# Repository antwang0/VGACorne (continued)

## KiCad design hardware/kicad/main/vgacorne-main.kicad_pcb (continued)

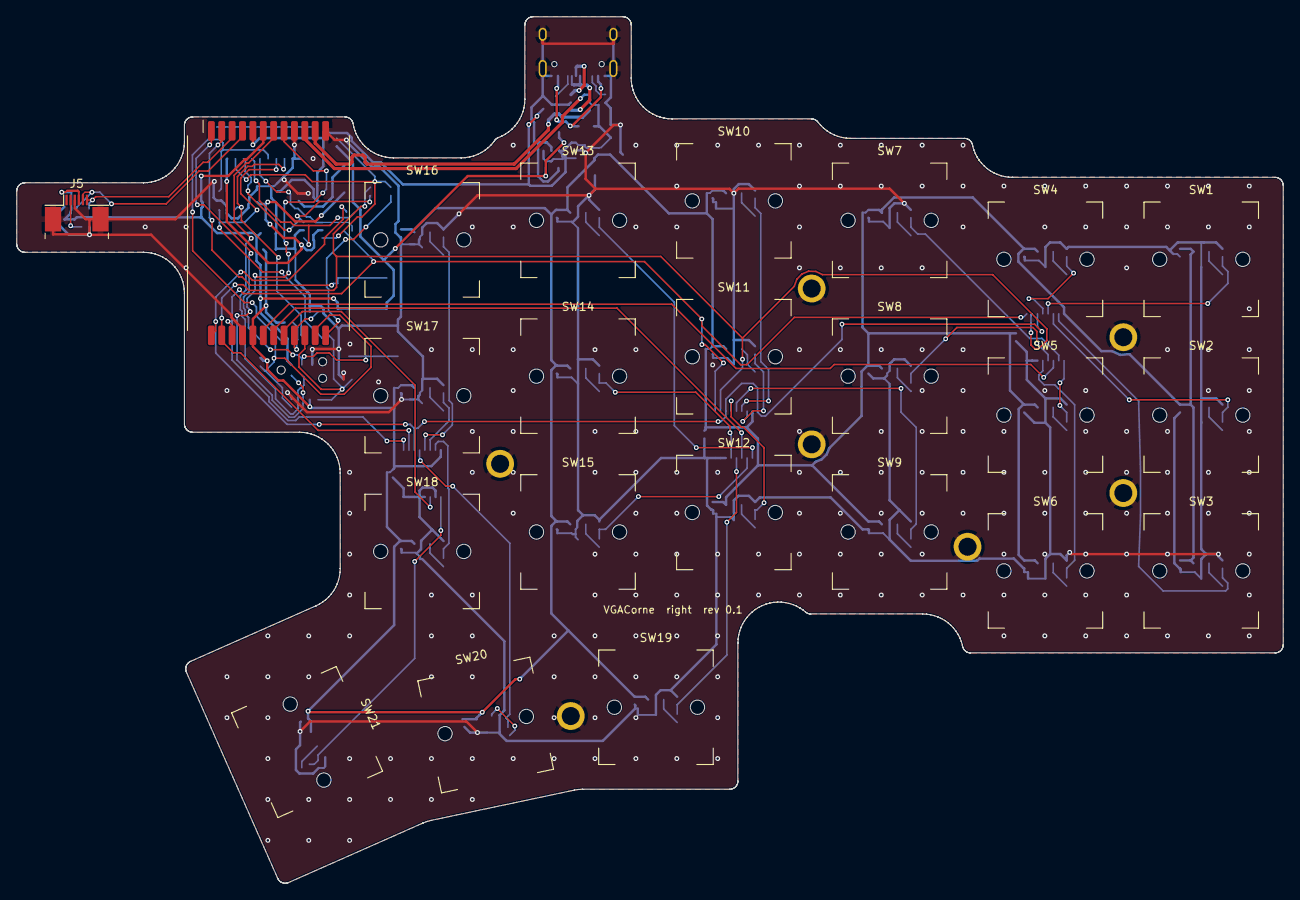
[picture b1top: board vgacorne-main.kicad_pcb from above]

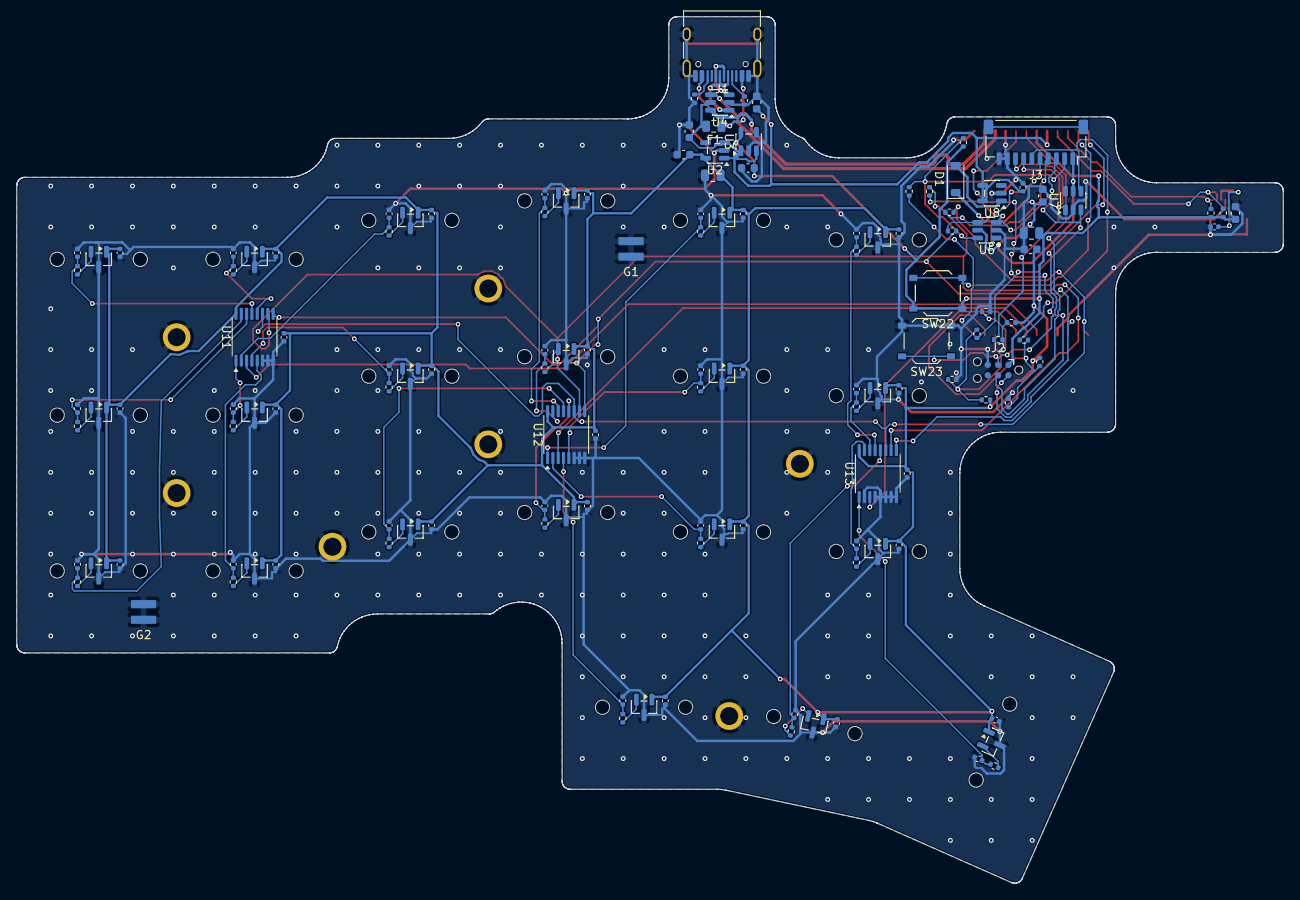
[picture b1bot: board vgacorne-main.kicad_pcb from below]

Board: 2 copper layers, 154.9 x 105.9 mm, 164 parts (134 on the bottom side), 79 nets.

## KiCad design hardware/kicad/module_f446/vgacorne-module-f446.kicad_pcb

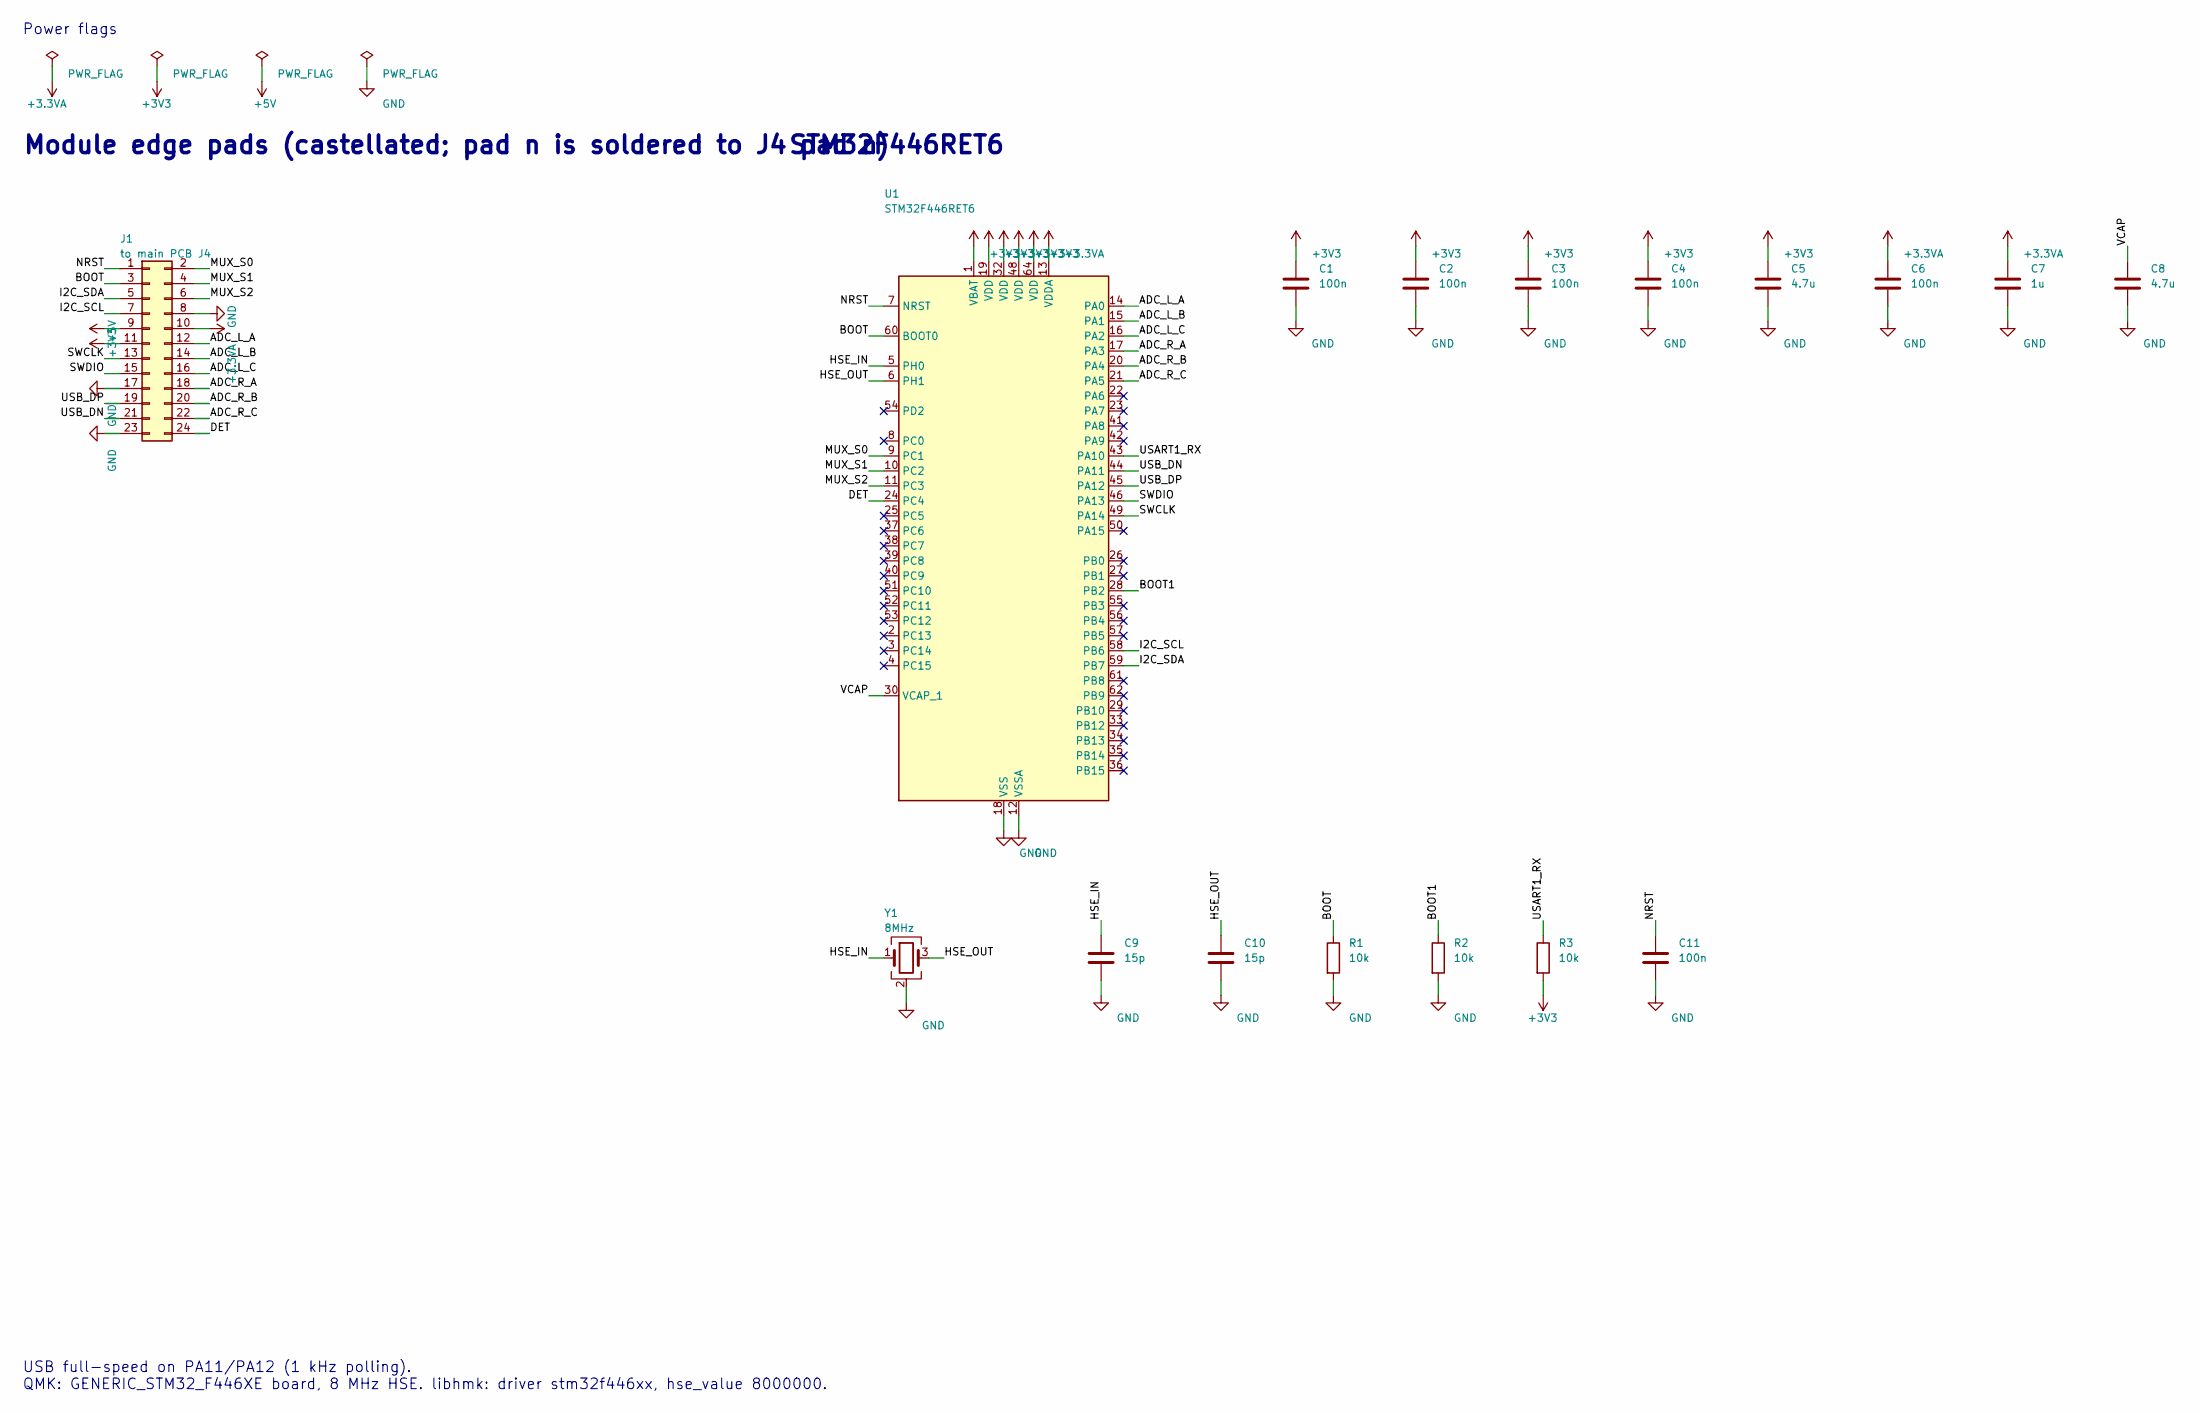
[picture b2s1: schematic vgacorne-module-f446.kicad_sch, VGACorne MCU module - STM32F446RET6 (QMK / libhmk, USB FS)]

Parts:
C1, C2, C3, C4, C6, C11: 100n; C_0402_1005Metric
C5, C8: 4.7u; C_0603_1608Metric
C7: 1u; C_0603_1608Metric
C9, C10: 15p; C_0402_1005Metric
J1: to main PCB J4; Module_Castellated_2x12_P1.27mm_19.4x25mm
R1, R2, R3: 10k; R_0402_1005Metric
U1: STM32F446RET6; LQFP-64_10x10mm_P0.5mm; MPN STM32F446RET6
Y1: 8MHz; Crystal_SMD_3225-4Pin_3.2x2.5mm; MPN X32258MOB4SI

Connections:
+3.3VA: C6.1, C7.1, J1.10, U1.13 (VDDA)
+3V3: C1.1, C2.1, C3.1, C4.1, C5.1, J1.11, R3.2, U1.1 (VBAT), U1.19 (VDD), U1.32 (VDD), U1.48 (VDD), U1.64 (VDD)
+5V: J1.9
/ADC_L_A: J1.12, U1.14 (PA0)
/ADC_L_B: J1.14, U1.15 (PA1)
/ADC_L_C: J1.16, U1.16 (PA2)
/ADC_R_A: J1.18, U1.17 (PA3)
/ADC_R_B: J1.20, U1.20 (PA4)
/ADC_R_C: J1.22, U1.21 (PA5)
/BOOT: J1.3, R1.1, U1.60 (BOOT0)
/BOOT1: R2.1, U1.28 (PB2)
/DET: J1.24, U1.24 (PC4)
/HSE_IN: C9.1, U1.5 (PH0), Y1.1
/HSE_OUT: C10.1, U1.6 (PH1), Y1.3
/I2C_SCL: J1.7, U1.58 (PB6)
/I2C_SDA: J1.5, U1.59 (PB7)
/MUX_S0: J1.2, U1.9 (PC1)
/MUX_S1: J1.4, U1.10 (PC2)
/MUX_S2: J1.6, U1.11 (PC3)
/NRST: C11.1, J1.1, U1.7 (NRST)
/SWCLK: J1.13, U1.49 (PA14)
/SWDIO: J1.15, U1.46 (PA13)
/USART1_RX: R3.1, U1.43 (PA10)
/USB_DN: J1.21, U1.44 (PA11)
/USB_DP: J1.19, U1.45 (PA12)
/VCAP: C8.1, U1.30 (VCAP_1)
GND: C1.2, C2.2, C3.2, C4.2, C5.2, C6.2, C7.2, C8.2, C9.2, C10.2, C11.2, J1.8, J1.17, J1.23, R1.2, R2.2, U1.12 (VSSA), U1.18 (VSS), U1.31 (VSS), U1.47 (VSS), U1.63 (VSS), Y1.2 (G), Y1.4 (G)

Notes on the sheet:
Module edge pads (castellated; pad n is soldered to J4 pad n)
STM32F446RET6
USB full-speed on PA11/PA12 (1 kHz polling). QMK: GENERIC_STM32_F446XE board, 8 MHz HSE. libhmk: driver stm32f446xx, hse_value 8000000.
Power flags

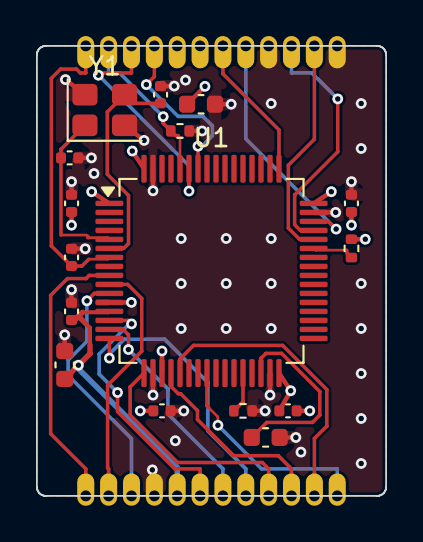
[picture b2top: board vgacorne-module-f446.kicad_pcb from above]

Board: 4 copper layers, 19.4 x 25.0 mm, 17 parts (0 on the bottom side), 26 nets.

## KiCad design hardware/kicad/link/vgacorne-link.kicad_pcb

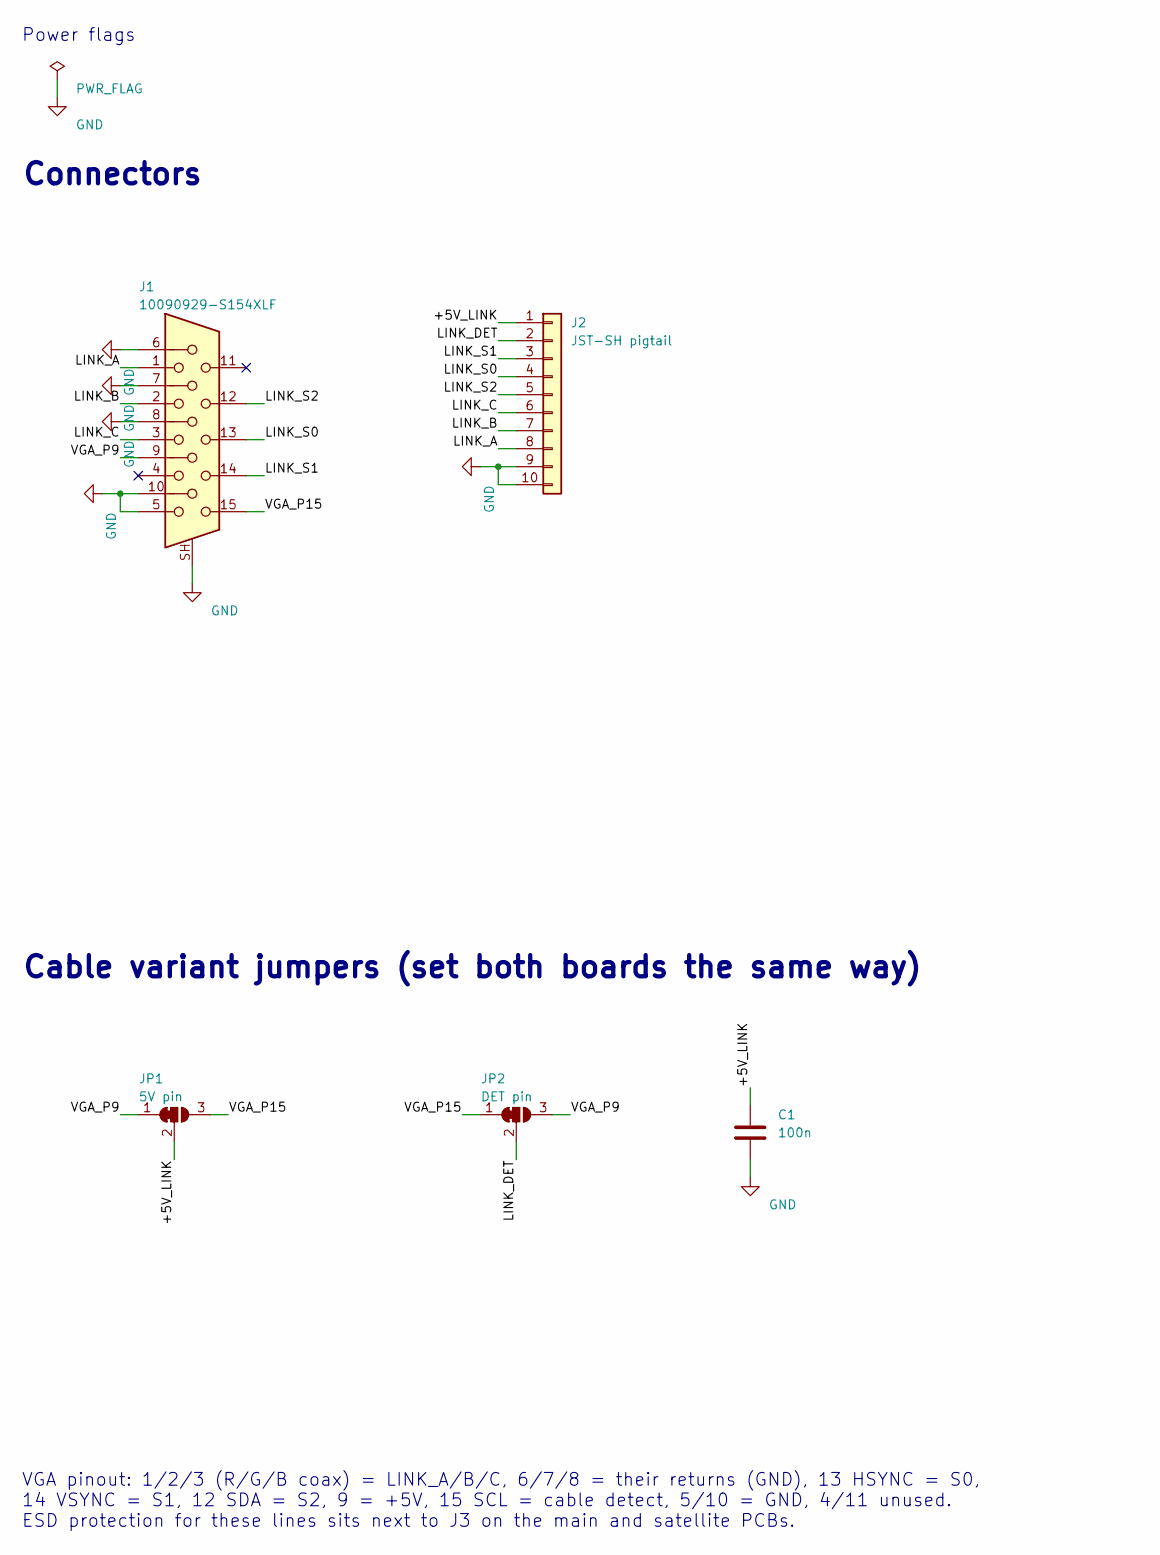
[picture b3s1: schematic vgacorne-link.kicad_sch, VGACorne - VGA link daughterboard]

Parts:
C1: 100n; C_0402_1005Metric
J1: 10090929-S154XLF; DSUB-15-HD_Socket_Vertical_P2.29x1.98mm_Amphenol_10090929; MPN Amphenol FCI 10090929-S154XLF
J2: JST-SH pigtail; WirePads_1x10_P1.6mm
JP1: 5V pin; SolderJumper-3_P1.3mm_Bridged12_RoundedPad1.0x1.5mm
JP2: DET pin; SolderJumper-3_P1.3mm_Bridged12_RoundedPad1.0x1.5mm

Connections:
/+5V_LINK: C1.1, J2.1, JP1.2 (C)
/LINK_A: J1.1, J2.8
/LINK_B: J1.2, J2.7
/LINK_C: J1.3, J2.6
/LINK_DET: J2.2, JP2.2 (C)
/LINK_S0: J1.13, J2.4
/LINK_S1: J1.14, J2.3
/LINK_S2: J1.12, J2.5
/VGA_P9: J1.9, JP1.1 (A), JP2.3 (B)
/VGA_P15: J1.15, JP1.3 (B), JP2.1 (A)
GND: C1.2, J1.5, J1.6, J1.7, J1.8, J1.10, J1.SH, J2.9, J2.10

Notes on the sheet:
Connectors
Cable variant jumpers (set both boards the same way)
VGA pinout: 1/2/3 (R/G/B coax) = LINK_A/B/C, 6/7/8 = their returns (GND), 13 HSYNC = S0, 14 VSYNC = S1, 12 SDA = S2, 9 = +5V, 15 SCL = cable detect, 5/10 = GND, 4/11 unused. ESD protection for these lines sits next to J3 on the main and satellite PCBs.
Power flags

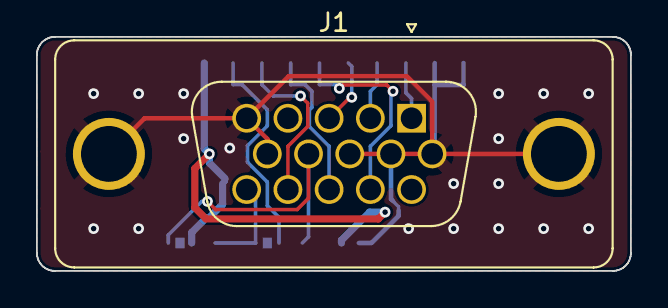
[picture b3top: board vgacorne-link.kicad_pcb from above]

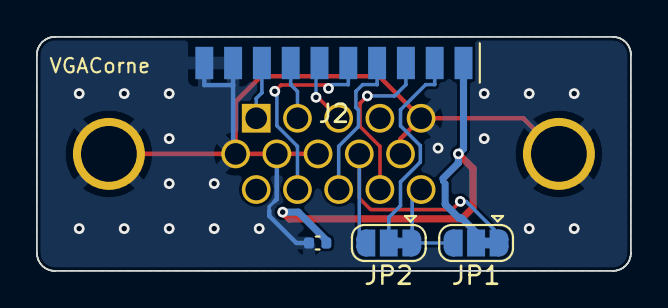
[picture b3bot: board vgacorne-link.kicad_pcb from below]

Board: 2 copper layers, 33.0 x 13.0 mm, 5 parts (4 on the bottom side), 11 nets.

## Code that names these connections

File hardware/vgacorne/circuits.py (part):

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# LQFP-64 pins used for keyboard signals. The AT32F405RCT7 and STM32F446RET6 share
# these pin numbers, so both modules (and their firmware configs) use the same map.
MCU_SIGNAL_PINS = {
    "14": "ADC_L_A", "15": "ADC_L_B", "16": "ADC_L_C",  # PA0..PA2: local muxes
    "17": "ADC_R_A", "20": "ADC_R_B", "21": "ADC_R_C",  # PA3..PA5: satellite muxes
    "9": "MUX_S0", "10": "MUX_S1", "11": "MUX_S2",  # PC1..PC3
    "24": "DET",  # PC4
    "7": "NRST", "60": "BOOT", "46": "SWDIO", "49": "SWCLK",  # NRST, BOOT0, PA13, PA14
    "58": "I2C_SCL", "59": "I2C_SDA",  # PB6/PB7: I2C1 (AF4 on the STM32, MUX4 on the AT32)
}
# firmware.py derives libhmk's select/input pin names from these by tracing the netlists.

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        R("R20", "4.7k", "I2C_SDA", "+3V3", "trackpad"),
        C("C16", "1u", "+3V3", "GND", "trackpad", fp=C0603),
    ]
    if "TP_NRST" in PAD.connector_pins.values():  # internal pull-up; Azoteq recommends 100 nF
        p.append(C("C17", "100n", "TP_NRST", "GND", "trackpad"))
    # Link to the satellite (via the VGA daughterboard)
    pull_up = SENSOR.invert_adc  # pull toward "released" when the cable is absent
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        Part("JP1", "Jumper:SolderJumper_3_Bridged12", "5V pin", "Jumper:SolderJumper-3_P1.3mm_Bridged12_RoundedPad1.0x1.5mm",
             {"1": "VGA_P9", "2": "+5V_LINK", "3": "VGA_P15"}, "jumpers",
             description="+5 V on VGA pin 9 (default) or pin 15 (for 3+4 cables without pin 9)"),
        Part("JP2", "Jumper:SolderJumper_3_Bridged12", "DET pin", "Jumper:SolderJumper-3_P1.3mm_Bridged12_RoundedPad1.0x1.5mm",
             {"1": "VGA_P15", "2": "LINK_DET", "3": "VGA_P9"}, "jumpers",
             description="Cable-detect on VGA pin 15 (default) or pin 9; always set opposite to JP1"),
        C("C1", "100n", "+5V_LINK", "GND", "jumpers"),
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        ("jumpers", "Cable variant jumpers (set both boards the same way)", (20.32, 150.0), 250),
    ]
    notes = [
        ("VGA pinout: 1/2/3 (R/G/B coax) = LINK_A/B/C, 6/7/8 = their returns (GND), 13 HSYNC = S0,\n"
         "14 VSYNC = S1, 12 SDA = S2, 9 = +5V, 15 SCL = cable detect, 5/10 = GND, 4/11 unused.\n"
         "ESD protection for these lines sits next to J3 on the main and satellite PCBs.", (20.32, 230.0)),
    ]
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        C("C9", XTAL_CAP, "HSE_IN", "GND", "mcu"), C("C10", XTAL_CAP, "HSE_OUT", "GND", "mcu"),
        R("R1", "10k", "BOOT", "GND", "mcu", description="BOOT0 pull-down"),
        R("R2", "10k", "BOOT1", "GND", "mcu",
          description="PB2/BOOT1 pull-down: BOOT0 = 1 only reaches the DFU bootloader with BOOT1 = 0 (RM0390)"),
        R("R3", "10k", "USART1_RX", "+3V3", "mcu",
          description="Holds the bootloader's unused USART1 RX (PA10) idle so noise can't select it (AN2606)"),
        C("C11", "100n", "NRST", "GND", "mcu"),
    ]
    return _module("vgacorne-module-f446", "VGACorne MCU module - STM32F446RET6 (QMK / libhmk, USB FS)", mcu, parts,
                   ["USB full-speed on PA11/PA12 (1 kHz polling).",
                    "QMK: GENERIC_STM32_F446XE board, 8 MHz HSE. libhmk: driver stm32f446xx, hse_value 8000000."])


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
